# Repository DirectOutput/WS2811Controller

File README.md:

# WS2811 Controller
Source Code for the Atmel based WS2811 controller.

This is just old code and board designs which I found on my backup disks. There are 3 different version of the code and several versions of the board design. In some directories there are a few word and pdf files that explain some of the details. Cant say for sure if some of all this any good and what that would be. 

The assembly code was written in Atmel Studio. The boards where made with Eagle.

Feel free to use it in any way you like. Unfortunately, I cant really help with questions, since I have not touched all this for the last 8 years.

7.8.2023

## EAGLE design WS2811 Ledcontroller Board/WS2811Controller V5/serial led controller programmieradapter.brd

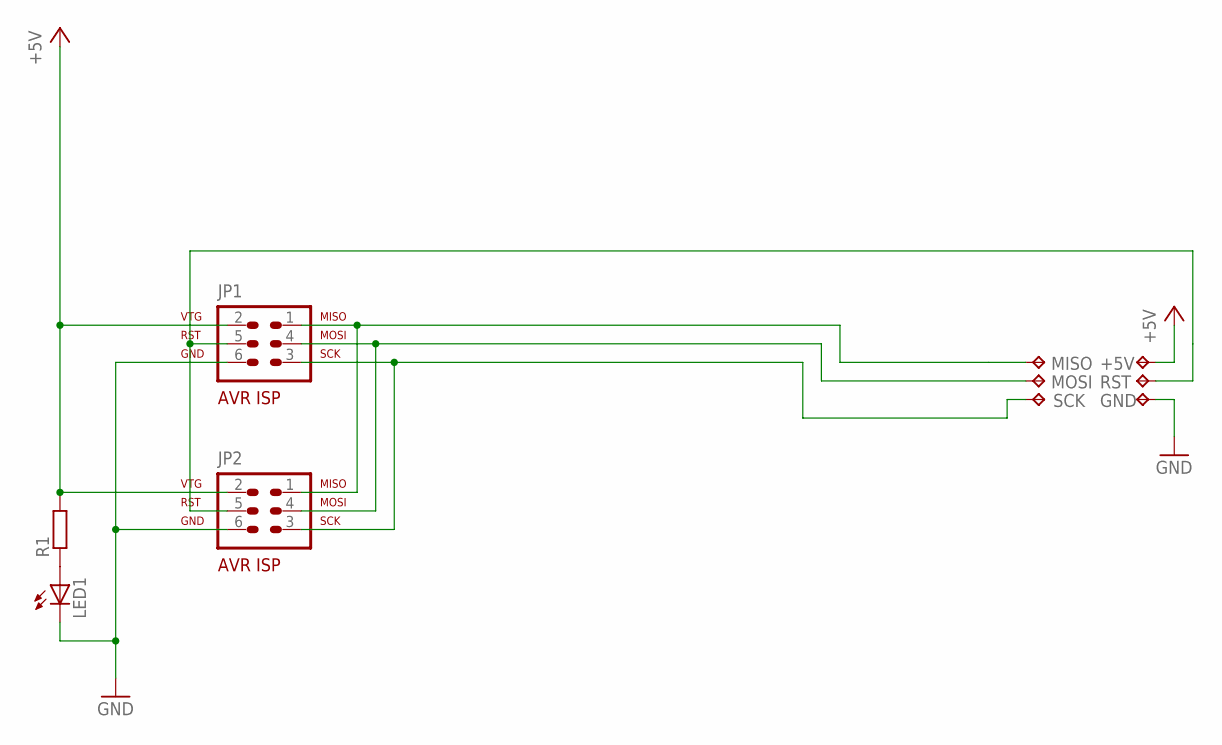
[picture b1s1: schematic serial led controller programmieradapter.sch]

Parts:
+5V: TPTP19R; TP19R
GND: TPTP19R; TP19R
JP1, JP2: AVR-ISP-6
LED1: LED3MM
MISO: TPTP19R; TP19R
MOSI: TPTP19R; TP19R
R1: R-EU_0207/10; 0207/10
RST: TPTP19R; TP19R
SCK: TPTP19R; TP19R

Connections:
+5V: +5V.TP, JP1.2, JP2.2, R1.2
GND: GND.TP, JP1.6, JP2.6, LED1.K (C)
MISO: JP1.1, JP2.1, MISO.TP
unnamed: LED1.A, R1.1
unnamed: JP1.4, JP2.4, MOSI.TP
RST: JP1.5, JP2.5, RST.TP
SCK: JP1.3, JP2.3, SCK.TP

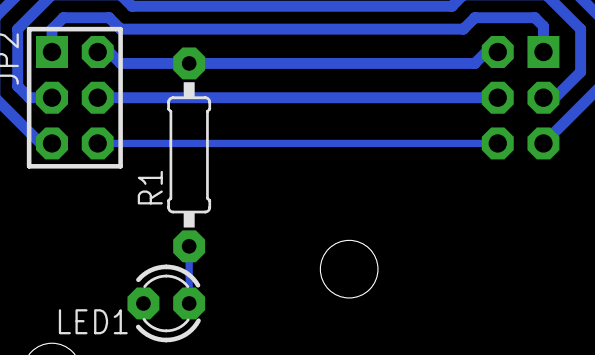
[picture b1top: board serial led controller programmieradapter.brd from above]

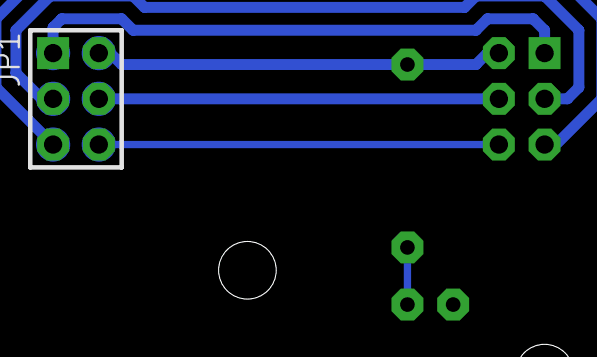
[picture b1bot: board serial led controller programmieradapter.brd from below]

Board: 2 copper layers, 10 parts (7 on the bottom side), 7 nets.

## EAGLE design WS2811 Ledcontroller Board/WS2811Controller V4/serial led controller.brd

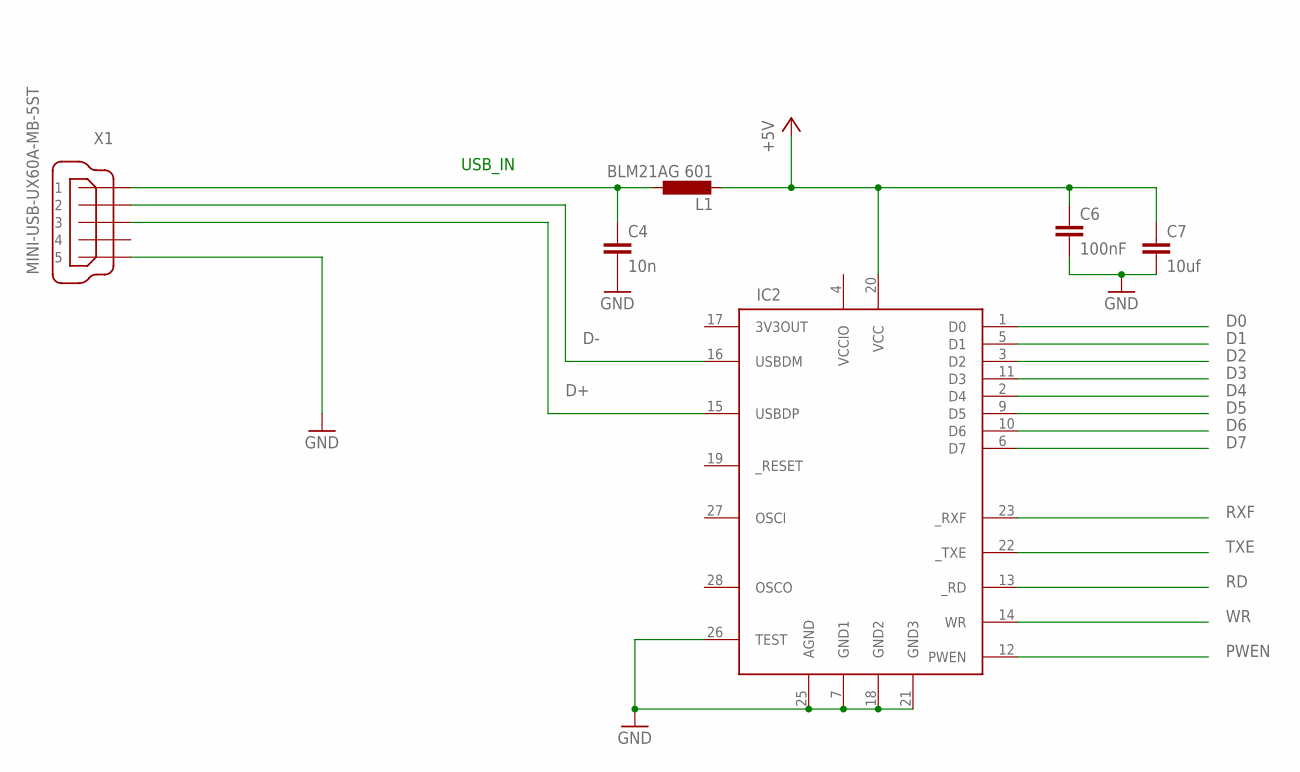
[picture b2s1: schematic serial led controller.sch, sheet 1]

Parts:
C4: 10n; C0603K
C6: 100nF; C0603K
C7: 10uf; C0603K
IC2: FT245RL; SSOP28DB
L1: BLM21AG 601; L805
X1: MINI-USB-UX60A-MB-5ST; UX60A-MB-5ST

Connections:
+5V: C6.1, C7.1, IC2.20 (VCC), L1.2; also elsewhere on the board
D0: IC2.1 (D0); also elsewhere on the board
D1: IC2.5 (D1); also elsewhere on the board
D2: IC2.3 (D2); also elsewhere on the board
D3: IC2.11 (D3); also elsewhere on the board
D4: IC2.2 (D4); also elsewhere on the board
D5: IC2.9 (D5); also elsewhere on the board
D6: IC2.10 (D6); also elsewhere on the board
D7: IC2.6 (D7); also elsewhere on the board
D+: IC2.15 (USBDP), X1.3
D-: IC2.16 (USBDM), X1.2
GND: C4.2, C6.2, C7.2, IC2.7 (GND1), IC2.18 (GND2), IC2.21 (GND3), IC2.25 (AGND), IC2.26 (TEST), X1.5; also elsewhere on the board
PWEN: IC2.12 (PWEN)
RD: IC2.13 (_RD); also elsewhere on the board
RXF: IC2.23 (_RXF); also elsewhere on the board
TXE: IC2.22 (_TXE); also elsewhere on the board
USBSUPPLY: C4.1, L1.1, X1.1
VCCIO: IC2.4 (VCCIO)
WR: IC2.14 (WR); also elsewhere on the board

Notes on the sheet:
USB_IN

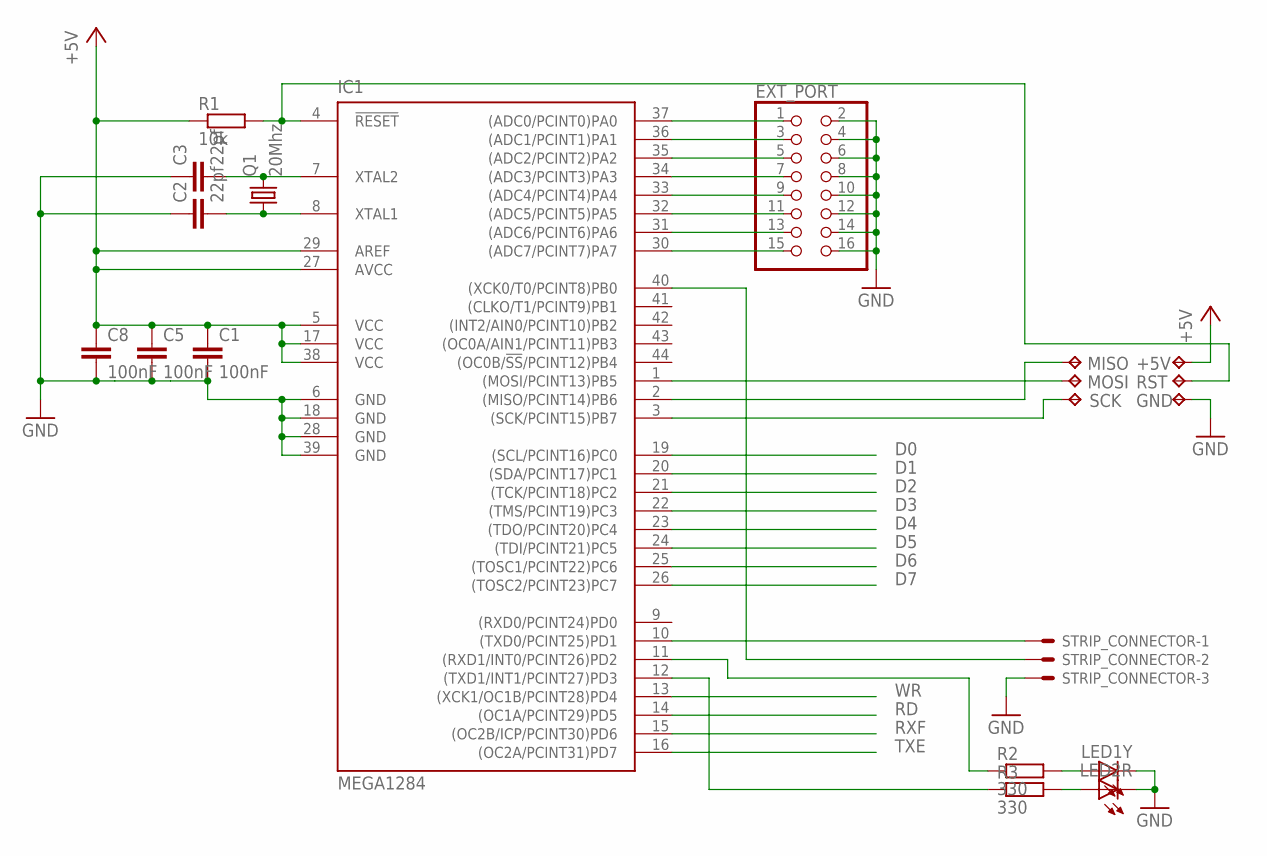
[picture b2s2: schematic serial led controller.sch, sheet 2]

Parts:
+5V: TPTP19R; TP19R
C1, C5, C8: 100nF; C0603K
C2, C3: 22pf; C0603K
EXT_PORT: PINHD-2X8; 2X08
GND: TPTP19R; TP19R
IC1: MEGA1284; TQFP44
LED1Y, LED2R: LEDCHIP-LED0603; CHIP-LED0603
MISO: TPTP19R; TP19R
MOSI: TPTP19R; TP19R
Q1: 20Mhz; SM49
R1: 10k; R0603
R2, R3: 330; R0603
RST: TPTP19R; TP19R
SCK: TPTP19R; TP19R
STRIP_CONNECTOR: 22-27-2031-03; 6410-03

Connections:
+5V: +5V.TP, C1.1, C5.1, C8.1, IC1.5 (VCC), IC1.17 (VCC), IC1.27 (AVCC), IC1.29 (AREF), IC1.38 (VCC), R1.1; also elsewhere on the board
CLOCK: IC1.40 ((XCK0/T0/PCINT8)PB0), STRIP_CONNECTOR.2
D0: IC1.19 ((SCL/PCINT16)PC0); also elsewhere on the board
D1: IC1.20 ((SDA/PCINT17)PC1); also elsewhere on the board
D2: IC1.21 ((TCK/PCINT18)PC2); also elsewhere on the board
D3: IC1.22 ((TMS/PCINT19)PC3); also elsewhere on the board
D4: IC1.23 ((TDO/PCINT20)PC4); also elsewhere on the board
D5: IC1.24 ((TDI/PCINT21)PC5); also elsewhere on the board
D6: IC1.25 ((TOSC1/PCINT22)PC6); also elsewhere on the board
D7: IC1.26 ((TOSC2/PCINT23)PC7); also elsewhere on the board
DATA: IC1.10 ((TXD0/PCINT25)PD1), STRIP_CONNECTOR.1
GND: C1.2, C2.1, C3.1, C5.2, C8.2, EXT_PORT.2, EXT_PORT.4, EXT_PORT.6, EXT_PORT.8, EXT_PORT.10, EXT_PORT.12, EXT_PORT.14, EXT_PORT.16, GND.TP, IC1.6 (GND), IC1.18 (GND), IC1.28 (GND), IC1.39 (GND), LED1Y.C, LED2R.C, STRIP_CONNECTOR.3; also elsewhere on the board
MISO: IC1.2 ((MISO/PCINT14)PB6), MISO.TP
MOSI: IC1.1 ((MOSI/PCINT13)PB5), MOSI.TP
unnamed: EXT_PORT.15, IC1.30 ((ADC7/PCINT7)PA7)
unnamed: EXT_PORT.13, IC1.31 ((ADC6/PCINT6)PA6)
unnamed: IC1.11 ((RXD1/INT0/PCINT26)PD2), R2.1
unnamed: EXT_PORT.11, IC1.32 ((ADC5/PCINT5)PA5)
unnamed: EXT_PORT.9, IC1.33 ((ADC4/PCINT4)PA4)
unnamed: IC1.12 ((TXD1/INT1/PCINT27)PD3), R3.1
unnamed: EXT_PORT.7, IC1.34 ((ADC3/PCINT3)PA3)
unnamed: C2.2, IC1.8 (XTAL1), Q1.1
unnamed: C3.2, IC1.7 (XTAL2), Q1.2
unnamed: EXT_PORT.5, IC1.35 ((ADC2/PCINT2)PA2)
unnamed: EXT_PORT.3, IC1.36 ((ADC1/PCINT1)PA1)
unnamed: EXT_PORT.1, IC1.37 ((ADC0/PCINT0)PA0)
unnamed: LED1Y.A, R2.2
unnamed: LED2R.A, R3.2
RD: IC1.14 ((OC1A/PCINT29)PD5); also elsewhere on the board
RST: IC1.4 (!RESET), R1.2, RST.TP
RXF: IC1.15 ((OC2B/ICP/PCINT30)PD6); also elsewhere on the board
SCK: IC1.3 ((SCK/PCINT15)PB7), SCK.TP
TXE: IC1.16 ((OC2A/PCINT31)PD7); also elsewhere on the board
WR: IC1.13 ((XCK1/OC1B/PCINT28)PD4); also elsewhere on the board

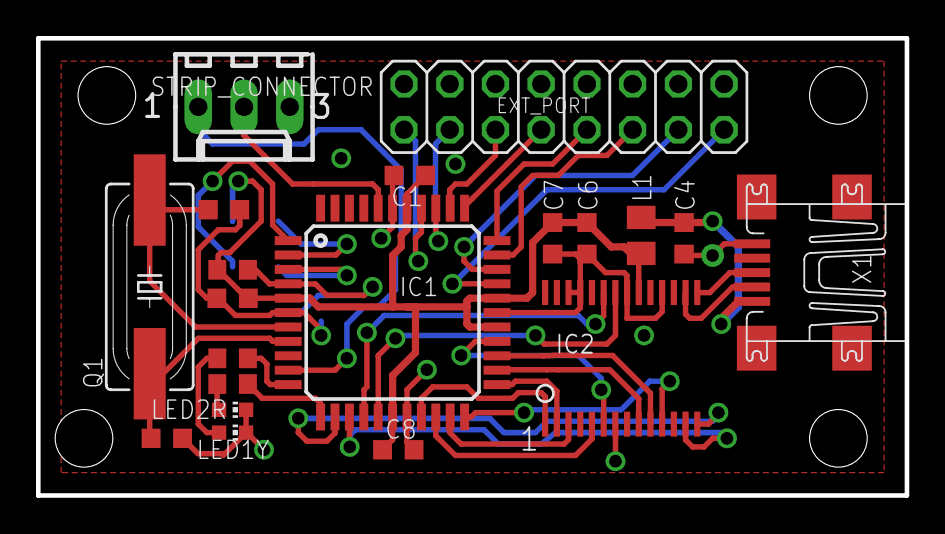
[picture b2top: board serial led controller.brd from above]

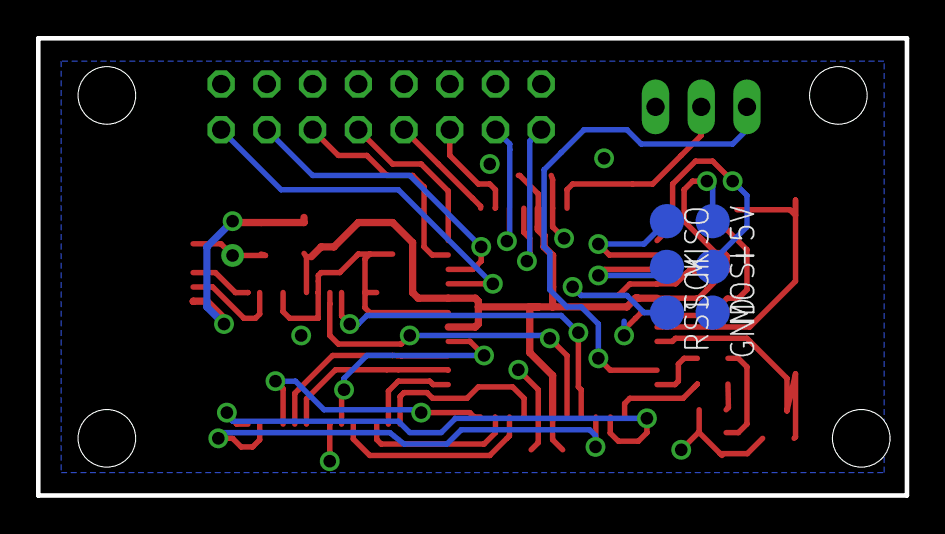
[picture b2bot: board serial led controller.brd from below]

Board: 2 copper layers, 48.3 x 25.4 mm, 26 parts (6 on the bottom side), 37 nets.

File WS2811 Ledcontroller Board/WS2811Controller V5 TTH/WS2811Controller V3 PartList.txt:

Partlist

Exported from WS2811Controller.sch at 29.04.2014 12:13:41

EAGLE Version 6.4.0 Copyright (c) 1988-2013 CadSoft

Assembly variant: 

Part             Value                 Device                Package                Library          Sheet

AVR-ISP                                AVR-ISP-6             AVR-ISP-6              0_avr            1
C1               100nF                 C-EU025-025X050       C025-025X050           0_Standard-Parts 1
C2               22pf                  C-EU025-025X050       C025-025X050           0_Standard-Parts 1
C3               22pf                  C-EU025-025X050       C025-025X050           0_Standard-Parts 1
C4               100nF                 C-EU025-025X050       C025-025X050           0_Standard-Parts 1
EXTCONNECTOR                           22-27-2101-10         6410-10                con-molex        1
IC1              MEGA164P/324P/644P-PU MEGA164P/324P/644P-PU DIL40                  0_avr            1
LED1                                   LED3MM                LED3MM                 0_Led            1
LED2                                   LED3MM                LED3MM                 0_Led            1
Q1               20Mhz                 CRYSTALHC49U-V        HC49U-V                0_tom parts      1
R1               10k                   R-EU_0207/10          0207/10                0_Standard-Parts 1
R2               330                   R-EU_0207/10          0207/10                0_Standard-Parts 1
R3               330                   R-EU_0207/10          0207/10                0_Standard-Parts 1
SPARKFUN_FT245RL                       FT245RL_BREAKOUTBOARD SPARKFUN_FT245RL_BOARD Sparkfun         1
STRIP1                                 22-27-2031-03         6410-03                con-molex        1

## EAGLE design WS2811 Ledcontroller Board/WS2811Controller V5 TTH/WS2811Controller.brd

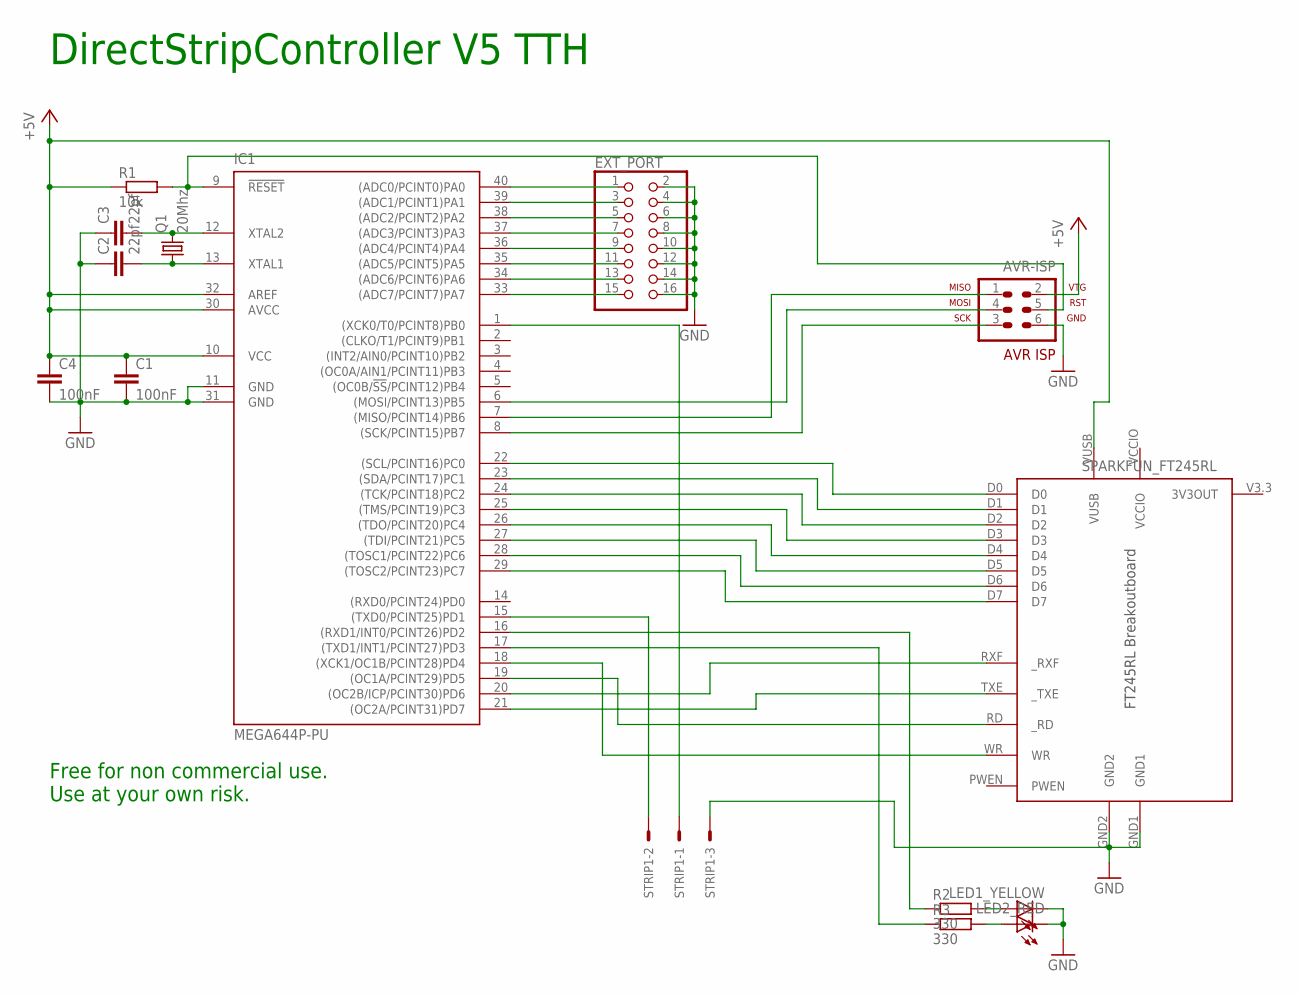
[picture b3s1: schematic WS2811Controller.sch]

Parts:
AVR-ISP: AVR-ISP-6
C1, C4: 100nF; C025-025X050
C2, C3: 22pf; C025-025X050
EXT_PORT: PINHD-2X8; 2X08
IC1: MEGA644P-PU; DIL40
LED1_YELLOW, LED2_RED: LED3MM
Q1: 20Mhz; HC49U-V
R1: 10k; 0207/10
R2, R3: 330; 0207/10
SPARKFUN_FT245RL: FT245RL_BREAKOUTBOARD; SPARKFUN_FT245RL_BOARD
STRIP1: 22-27-2031-03; 6410-03

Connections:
+5V: AVR-ISP.2, C1.1, C4.1, IC1.10 (VCC), IC1.30 (AVCC), IC1.32 (AREF), R1.1, SPARKFUN_FT245RL.VUSB
DATA0: IC1.22 ((SCL/PCINT16)PC0), SPARKFUN_FT245RL.D0
DATA1: IC1.23 ((SDA/PCINT17)PC1), SPARKFUN_FT245RL.D1
DATA2: IC1.24 ((TCK/PCINT18)PC2), SPARKFUN_FT245RL.D2
DATA3: IC1.25 ((TMS/PCINT19)PC3), SPARKFUN_FT245RL.D3
DATA4: IC1.26 ((TDO/PCINT20)PC4), SPARKFUN_FT245RL.D4
DATA5: IC1.27 ((TDI/PCINT21)PC5), SPARKFUN_FT245RL.D5
DATA6: IC1.28 ((TOSC1/PCINT22)PC6), SPARKFUN_FT245RL.D6
DATA7: IC1.29 ((TOSC2/PCINT23)PC7), SPARKFUN_FT245RL.D7
GND: AVR-ISP.6, C1.2, C2.1, C3.1, C4.2, EXT_PORT.2, EXT_PORT.4, EXT_PORT.6, EXT_PORT.8, EXT_PORT.10, EXT_PORT.12, EXT_PORT.14, EXT_PORT.16, IC1.11 (GND), IC1.31 (GND), LED1_YELLOW.K (C), LED2_RED.K (C), SPARKFUN_FT245RL.GND1, SPARKFUN_FT245RL.GND2, STRIP1.3
MISO: AVR-ISP.1, IC1.7 ((MISO/PCINT14)PB6)
MOSI: AVR-ISP.4, IC1.6 ((MOSI/PCINT13)PB5)
unnamed: IC1.16 ((RXD1/INT0/PCINT26)PD2), R2.1
unnamed: IC1.17 ((TXD1/INT1/PCINT27)PD3), R3.1
unnamed: C2.2, IC1.13 (XTAL1), Q1.1
unnamed: C3.2, IC1.12 (XTAL2), Q1.2
unnamed: LED1_YELLOW.A, R2.2
unnamed: LED2_RED.A, R3.2
unnamed: EXT_PORT.1, IC1.40 ((ADC0/PCINT0)PA0)
unnamed: EXT_PORT.3, IC1.39 ((ADC1/PCINT1)PA1)
unnamed: EXT_PORT.5, IC1.38 ((ADC2/PCINT2)PA2)
unnamed: EXT_PORT.7, IC1.37 ((ADC3/PCINT3)PA3)
unnamed: EXT_PORT.9, IC1.36 ((ADC4/PCINT4)PA4)
unnamed: EXT_PORT.11, IC1.35 ((ADC5/PCINT5)PA5)
unnamed: EXT_PORT.13, IC1.34 ((ADC6/PCINT6)PA6)
unnamed: EXT_PORT.15, IC1.33 ((ADC7/PCINT7)PA7)
RD: IC1.19 ((OC1A/PCINT29)PD5), SPARKFUN_FT245RL.RD (_RD)
RESET: AVR-ISP.5, IC1.9 (!RESET), R1.2
RXF: IC1.20 ((OC2B/ICP/PCINT30)PD6), SPARKFUN_FT245RL.RXF (_RXF)
SCK: AVR-ISP.3, IC1.8 ((SCK/PCINT15)PB7)
STRIP_CLOCK: IC1.1 ((XCK0/T0/PCINT8)PB0), STRIP1.1
STRIP_DATA: IC1.15 ((TXD0/PCINT25)PD1), STRIP1.2
TXE: IC1.21 ((OC2A/PCINT31)PD7), SPARKFUN_FT245RL.TXE (_TXE)
VCCIO: SPARKFUN_FT245RL.VCCIO
WR: IC1.18 ((XCK1/OC1B/PCINT28)PD4), SPARKFUN_FT245RL.WR

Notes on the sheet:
DirectStripController V5 TTH
Free for non commercial use. Use at your own risk.

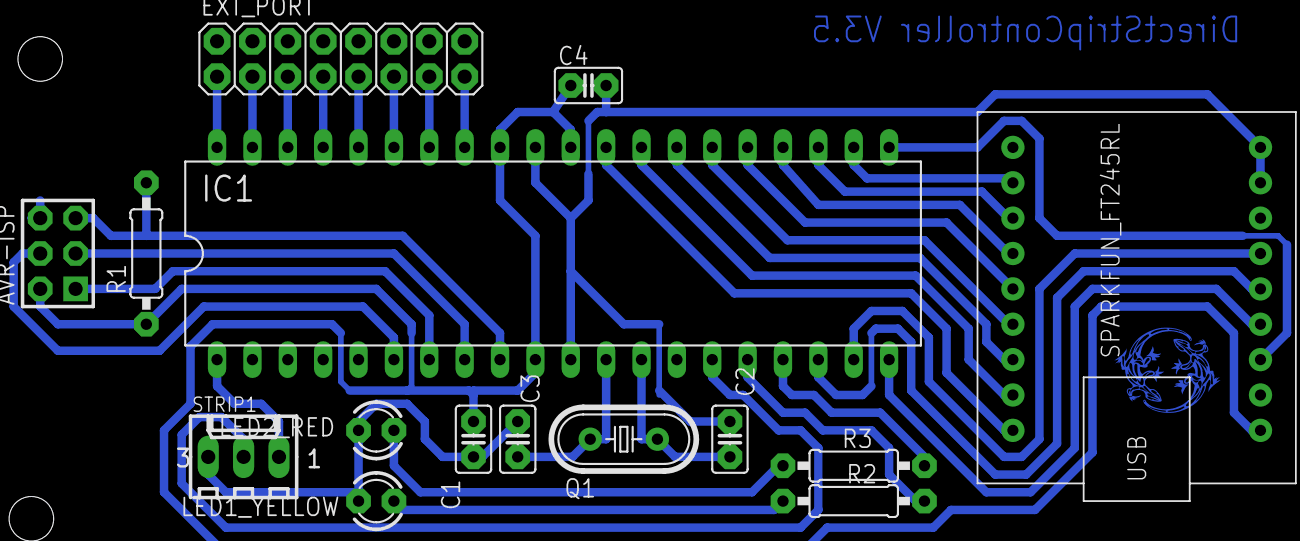
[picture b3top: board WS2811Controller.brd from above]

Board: 2 copper layers, 16 parts (0 on the bottom side), 34 nets.

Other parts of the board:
U$1: BOTTOM_DOUBLE_LIZARD_300
